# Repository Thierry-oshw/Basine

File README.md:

# Basine
Basine est une carte supportant Ultrogothe et les allumettes. Plusieurs variantes prévues.

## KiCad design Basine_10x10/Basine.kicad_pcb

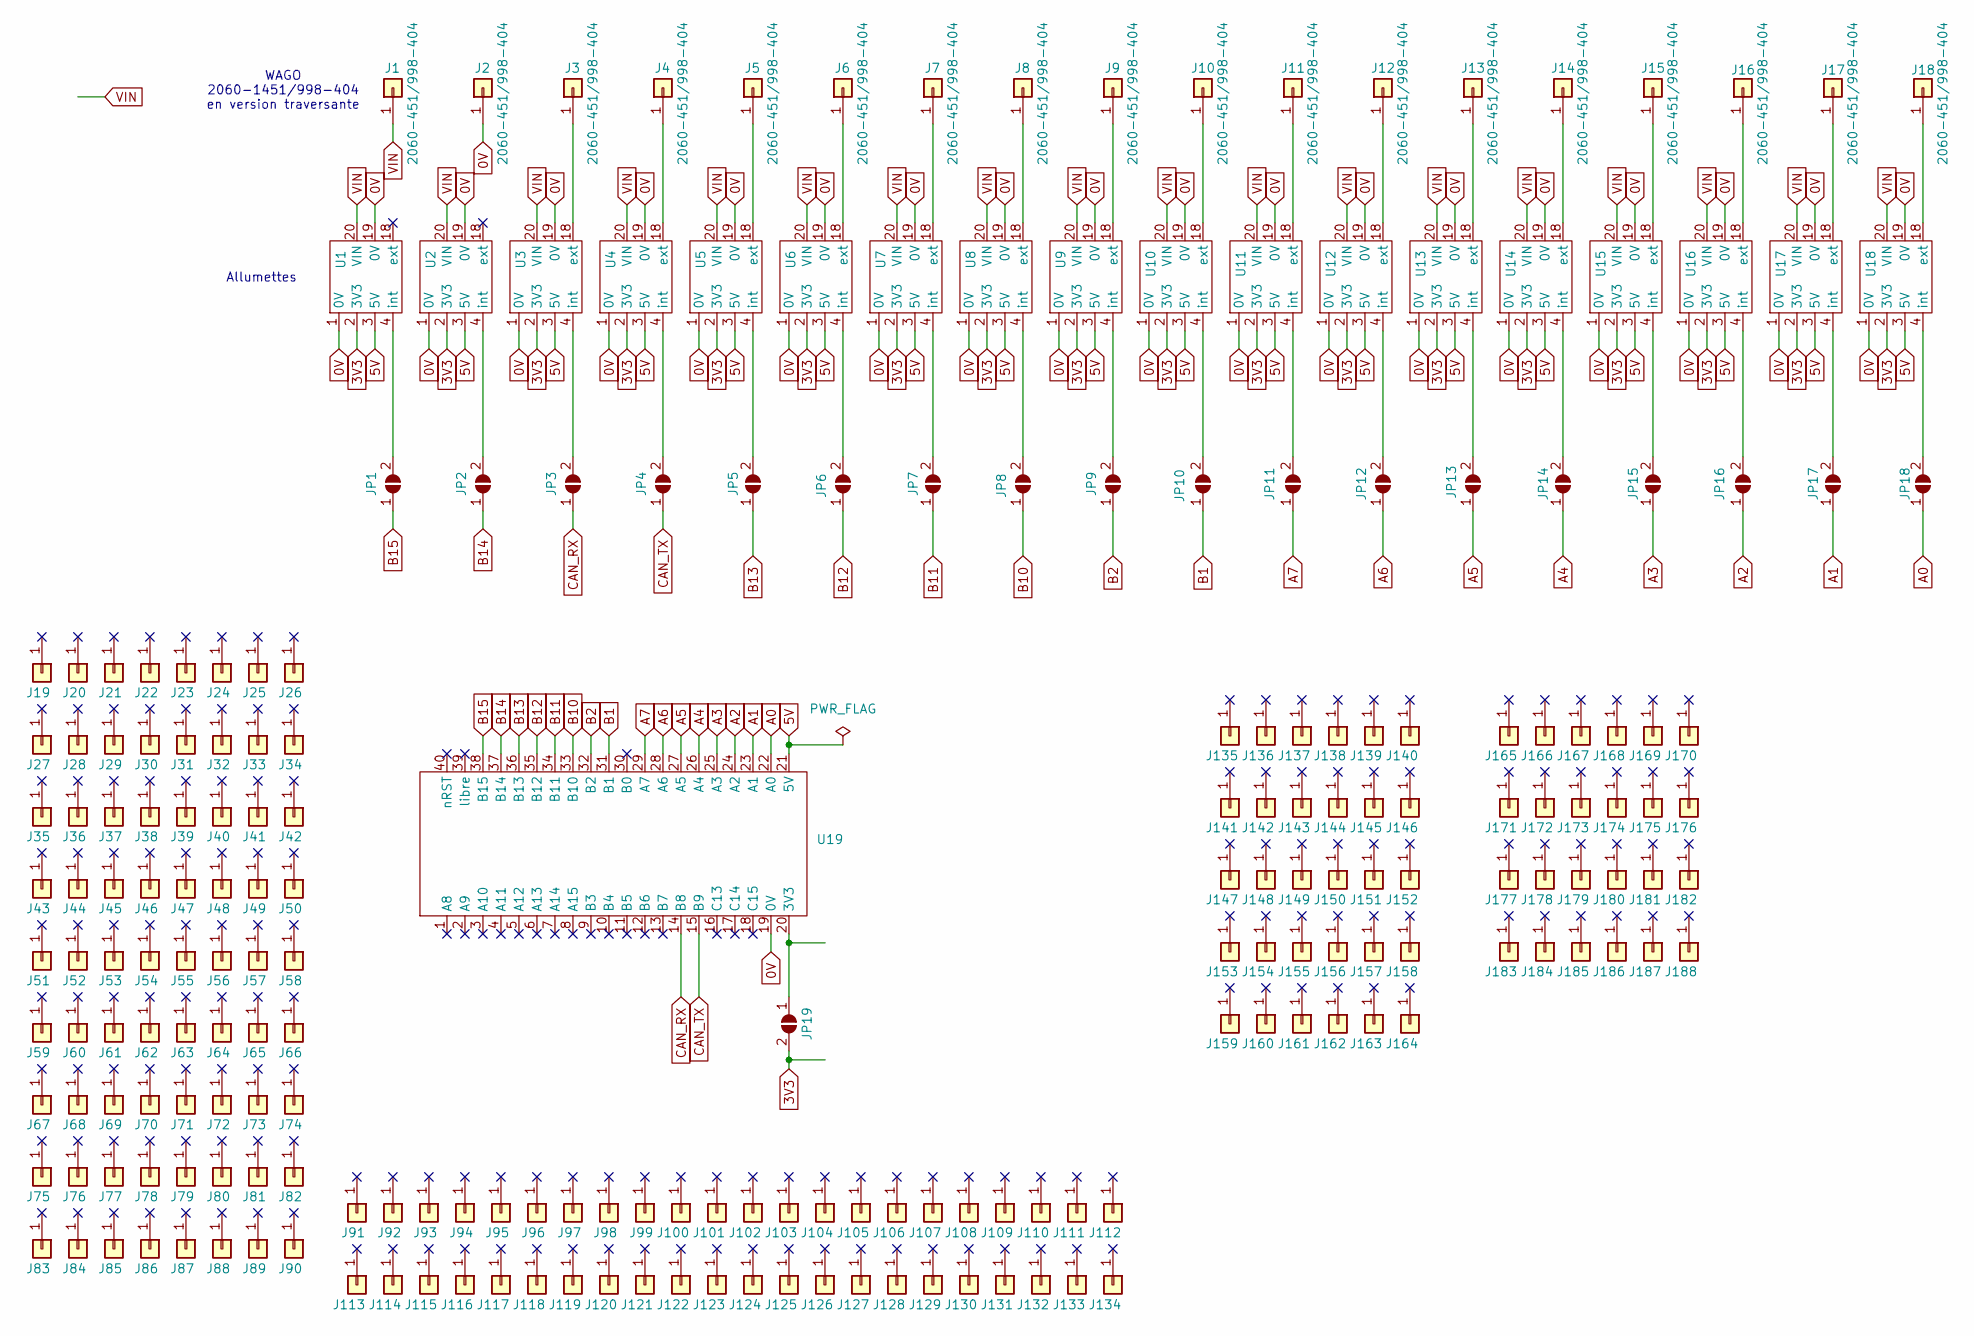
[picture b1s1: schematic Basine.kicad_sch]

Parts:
J1, J2, J3, J4, J5, J6, J7, J8, J9, J10, J11, J12, J13, J14, J15, J16, J17, J18: 2060-451/998-404; Conn_bornier_et_wago
J19, J20, J21, J22, J23, J24, J25, J26, J27, J28, J29, J30, J31, J32, J33, J34, J35, J36, J37, J38, J39, J40, J41, J42, J43, J44, J45, J46, J47, J48, J49, J50, J51, J52, J53, J54, J55, J56, J57, J58, J59, J60, J61, J62, J63, J64, J65, J66, J67, J68, J69, J70, J71, J72, J73, J74, J75, J76, J77, J78, J79, J80, J81, J82, J83, J84, J85, J86, J87, J88, J89, J90, J91, J92, J93, J94, J95, J96, J97, J98, J99, J100, J101, J102, J103, J104, J105, J106, J107, J108, J109, J110, J111, J112, J113, J114, J115, J116, J117, J118, J119, J120, J121, J122, J123, J124, J125, J126, J127, J128, J129, J130, J131, J132, J133, J134, J135, J136, J137, J138, J139, J140, J141, J142, J143, J144, J145, J146, J147, J148, J149, J150, J151, J152, J153, J154, J155, J156, J157, J158, J159, J160, J161, J162, J163, J164, J165, J166, J167, J168, J169, J170, J171, J172, J173, J174, J175, J176, J177, J178, J179, J180, J181, J182, J183, J184, J185, J186, J187, J188: Pastille; Pastille_carree
JP1, JP2, JP3, JP4, JP5, JP6, JP7, JP8, JP9, JP10, JP11, JP12, JP13, JP14, JP15, JP16, JP17, JP18, JP19: SolderJumper_2_Open; SolderJumper-2_P1.3mm_Open_TrianglePad1.0x1.5mm
U1, U2, U3, U4, U5, U6, U7, U8, U9, U10, U11, U12, U13, U14, U15, U16, U17, U18: Allumette
U19: Ultrogothe

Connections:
0V: J2.1, U1.1 (0V), U1.19 (0V), U2.1 (0V), U2.19 (0V), U3.1 (0V), U3.19 (0V), U4.1 (0V), U4.19 (0V), U5.1 (0V), U5.19 (0V), U6.1 (0V), U6.19 (0V), U7.1 (0V), U7.19 (0V), U8.1 (0V), U8.19 (0V), U9.1 (0V), U9.19 (0V), U10.1 (0V), U10.19 (0V), U11.1 (0V), U11.19 (0V), U12.1 (0V), U12.19 (0V), U13.1 (0V), U13.19 (0V), U14.1 (0V), U14.19 (0V), U15.1 (0V), U15.19 (0V), U16.1 (0V), U16.19 (0V), U17.1 (0V), U17.19 (0V), U18.1 (0V), U18.19 (0V), U19.19 (0V)
3V3: JP19.2 (B), U1.2 (3V3), U2.2 (3V3), U3.2 (3V3), U4.2 (3V3), U5.2 (3V3), U6.2 (3V3), U7.2 (3V3), U8.2 (3V3), U9.2 (3V3), U10.2 (3V3), U11.2 (3V3), U12.2 (3V3), U13.2 (3V3), U14.2 (3V3), U15.2 (3V3), U16.2 (3V3), U17.2 (3V3), U18.2 (3V3)
5V: U1.3 (5V), U2.3 (5V), U3.3 (5V), U4.3 (5V), U5.3 (5V), U6.3 (5V), U7.3 (5V), U8.3 (5V), U9.3 (5V), U10.3 (5V), U11.3 (5V), U12.3 (5V), U13.3 (5V), U14.3 (5V), U15.3 (5V), U16.3 (5V), U17.3 (5V), U18.3 (5V), U19.21 (5V)
A0: JP18.1 (A), U19.22 (A0)
A1: JP17.1 (A), U19.23 (A1)
A2: JP16.1 (A), U19.24 (A2)
A3: JP15.1 (A), U19.25 (A3)
A4: JP14.1 (A), U19.26 (A4)
A5: JP13.1 (A), U19.27 (A5)
A6: JP12.1 (A), U19.28 (A6)
A7: JP11.1 (A), U19.29 (A7)
B1: JP10.1 (A), U19.31 (B1)
B2: JP9.1 (A), U19.32 (B2)
B10: JP8.1 (A), U19.33 (B10)
B11: JP7.1 (A), U19.34 (B11)
B12: JP6.1 (A), U19.35 (B12)
B13: JP5.1 (A), U19.36 (B13)
B14: JP2.1 (A), U19.37 (B14)
B15: JP1.1 (A), U19.38 (B15)
CAN_RX: JP3.1 (A), U19.14 (B8)
CAN_TX: JP4.1 (A), U19.15 (B9)
unnamed: J3.1, U3.18 (ext)
unnamed: J4.1, U4.18 (ext)
unnamed: J5.1, U5.18 (ext)
unnamed: J6.1, U6.18 (ext)
unnamed: J7.1, U7.18 (ext)
unnamed: J8.1, U8.18 (ext)
unnamed: J9.1, U9.18 (ext)
unnamed: J10.1, U10.18 (ext)
unnamed: J11.1, U11.18 (ext)
unnamed: J12.1, U12.18 (ext)
unnamed: J13.1, U13.18 (ext)
unnamed: J14.1, U14.18 (ext)
unnamed: J15.1, U15.18 (ext)
unnamed: J16.1, U16.18 (ext)
unnamed: J17.1, U17.18 (ext)
unnamed: J18.1, U18.18 (ext)
unnamed: JP1.2 (B), U1.4 (int)
unnamed: JP2.2 (B), U2.4 (int)
unnamed: JP3.2 (B), U3.4 (int)
unnamed: JP4.2 (B), U4.4 (int)
unnamed: JP5.2 (B), U5.4 (int)
unnamed: JP6.2 (B), U6.4 (int)
unnamed: JP7.2 (B), U7.4 (int)
unnamed: JP8.2 (B), U8.4 (int)
unnamed: JP9.2 (B), U9.4 (int)
unnamed: JP10.2 (B), U10.4 (int)
unnamed: JP11.2 (B), U11.4 (int)
unnamed: JP12.2 (B), U12.4 (int)
unnamed: JP13.2 (B), U13.4 (int)
unnamed: JP14.2 (B), U14.4 (int)
unnamed: JP15.2 (B), U15.4 (int)
unnamed: JP16.2 (B), U16.4 (int)
unnamed: JP17.2 (B), U17.4 (int)
unnamed: JP18.2 (B), U18.4 (int)
unnamed: JP19.1 (A), U19.20 (3V3)
VIN: J1.1, U1.20 (VIN), U2.20 (VIN), U3.20 (VIN), U4.20 (VIN), U5.20 (VIN), U6.20 (VIN), U7.20 (VIN), U8.20 (VIN), U9.20 (VIN), U10.20 (VIN), U11.20 (VIN), U12.20 (VIN), U13.20 (VIN), U14.20 (VIN), U15.20 (VIN), U16.20 (VIN), U17.20 (VIN), U18.20 (VIN)

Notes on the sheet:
WAGO 2060-1451/998-404 en version traversante
Allumettes

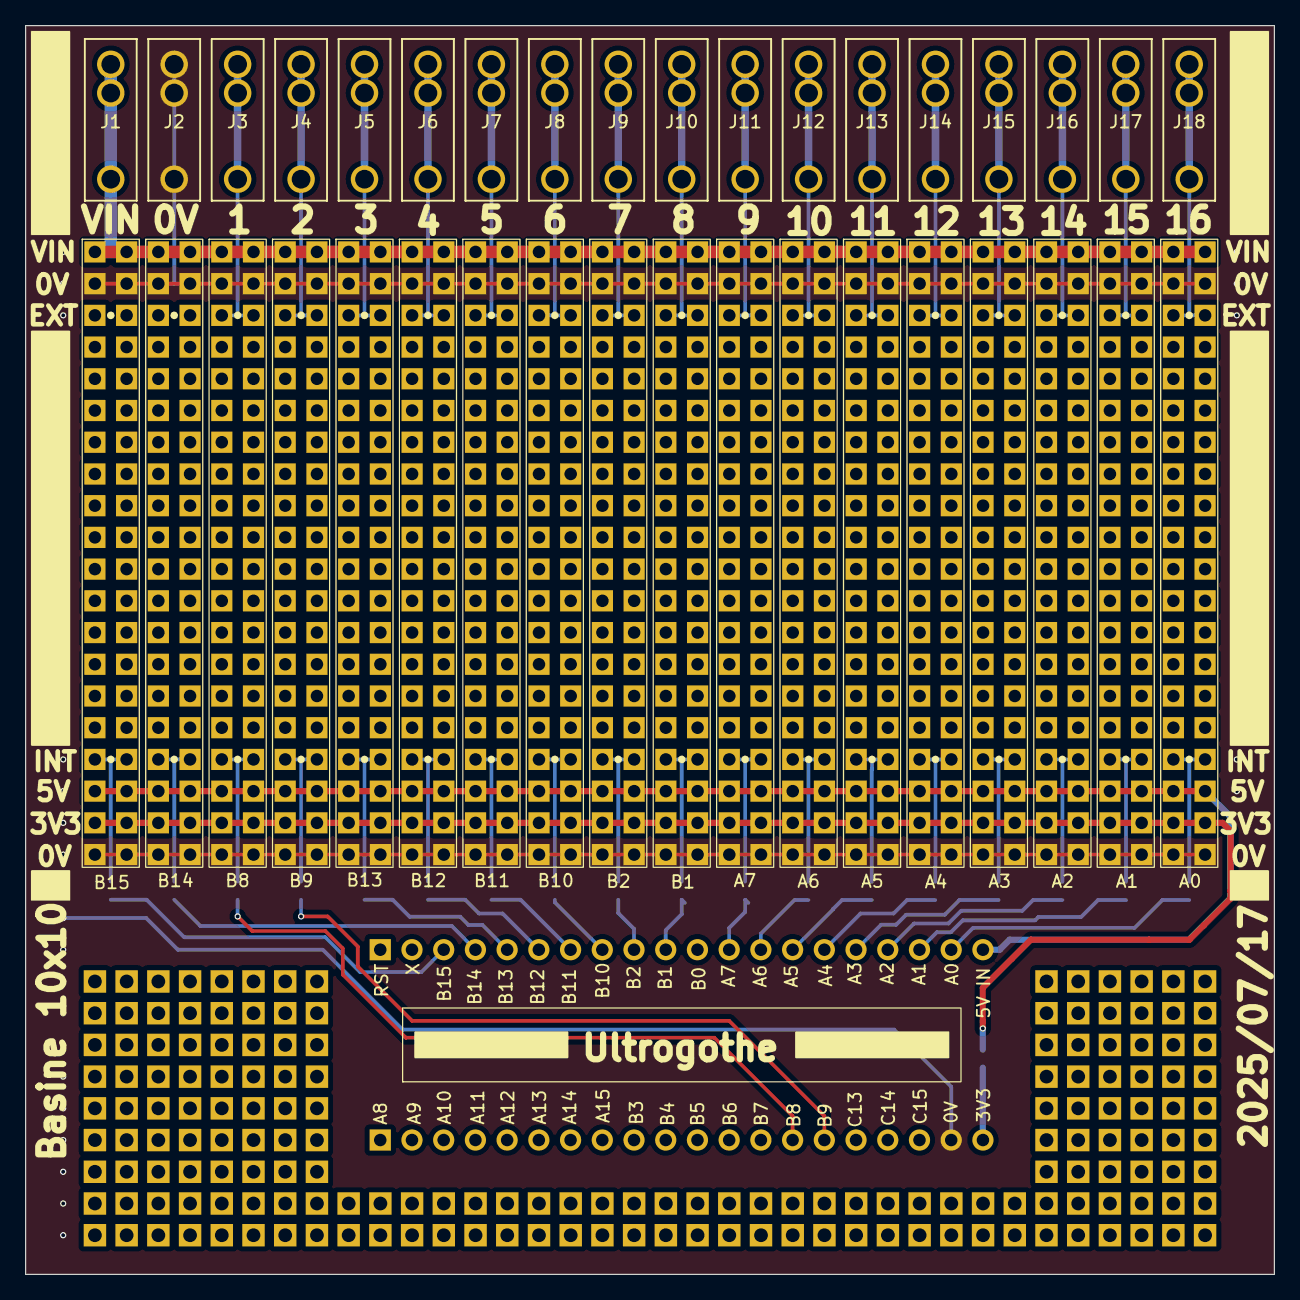
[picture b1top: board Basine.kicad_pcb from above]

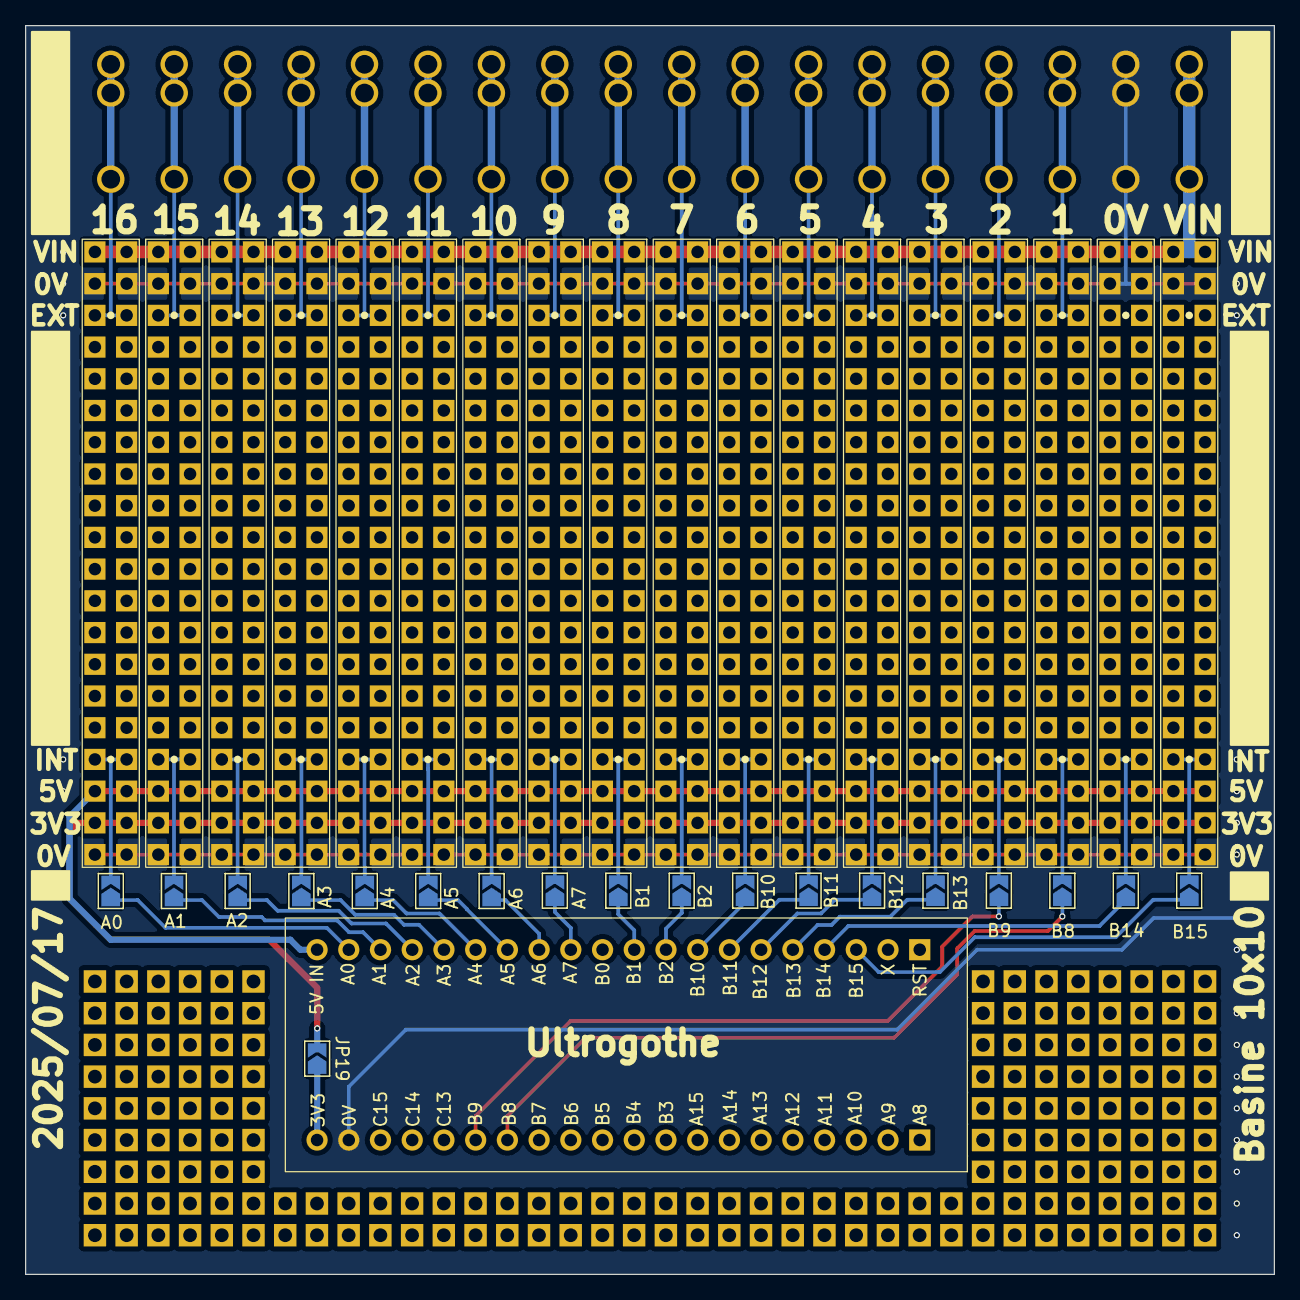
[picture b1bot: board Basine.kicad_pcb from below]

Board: 2 copper layers, 100.0 x 100.0 mm, 226 parts (19 on the bottom side), 57 nets.

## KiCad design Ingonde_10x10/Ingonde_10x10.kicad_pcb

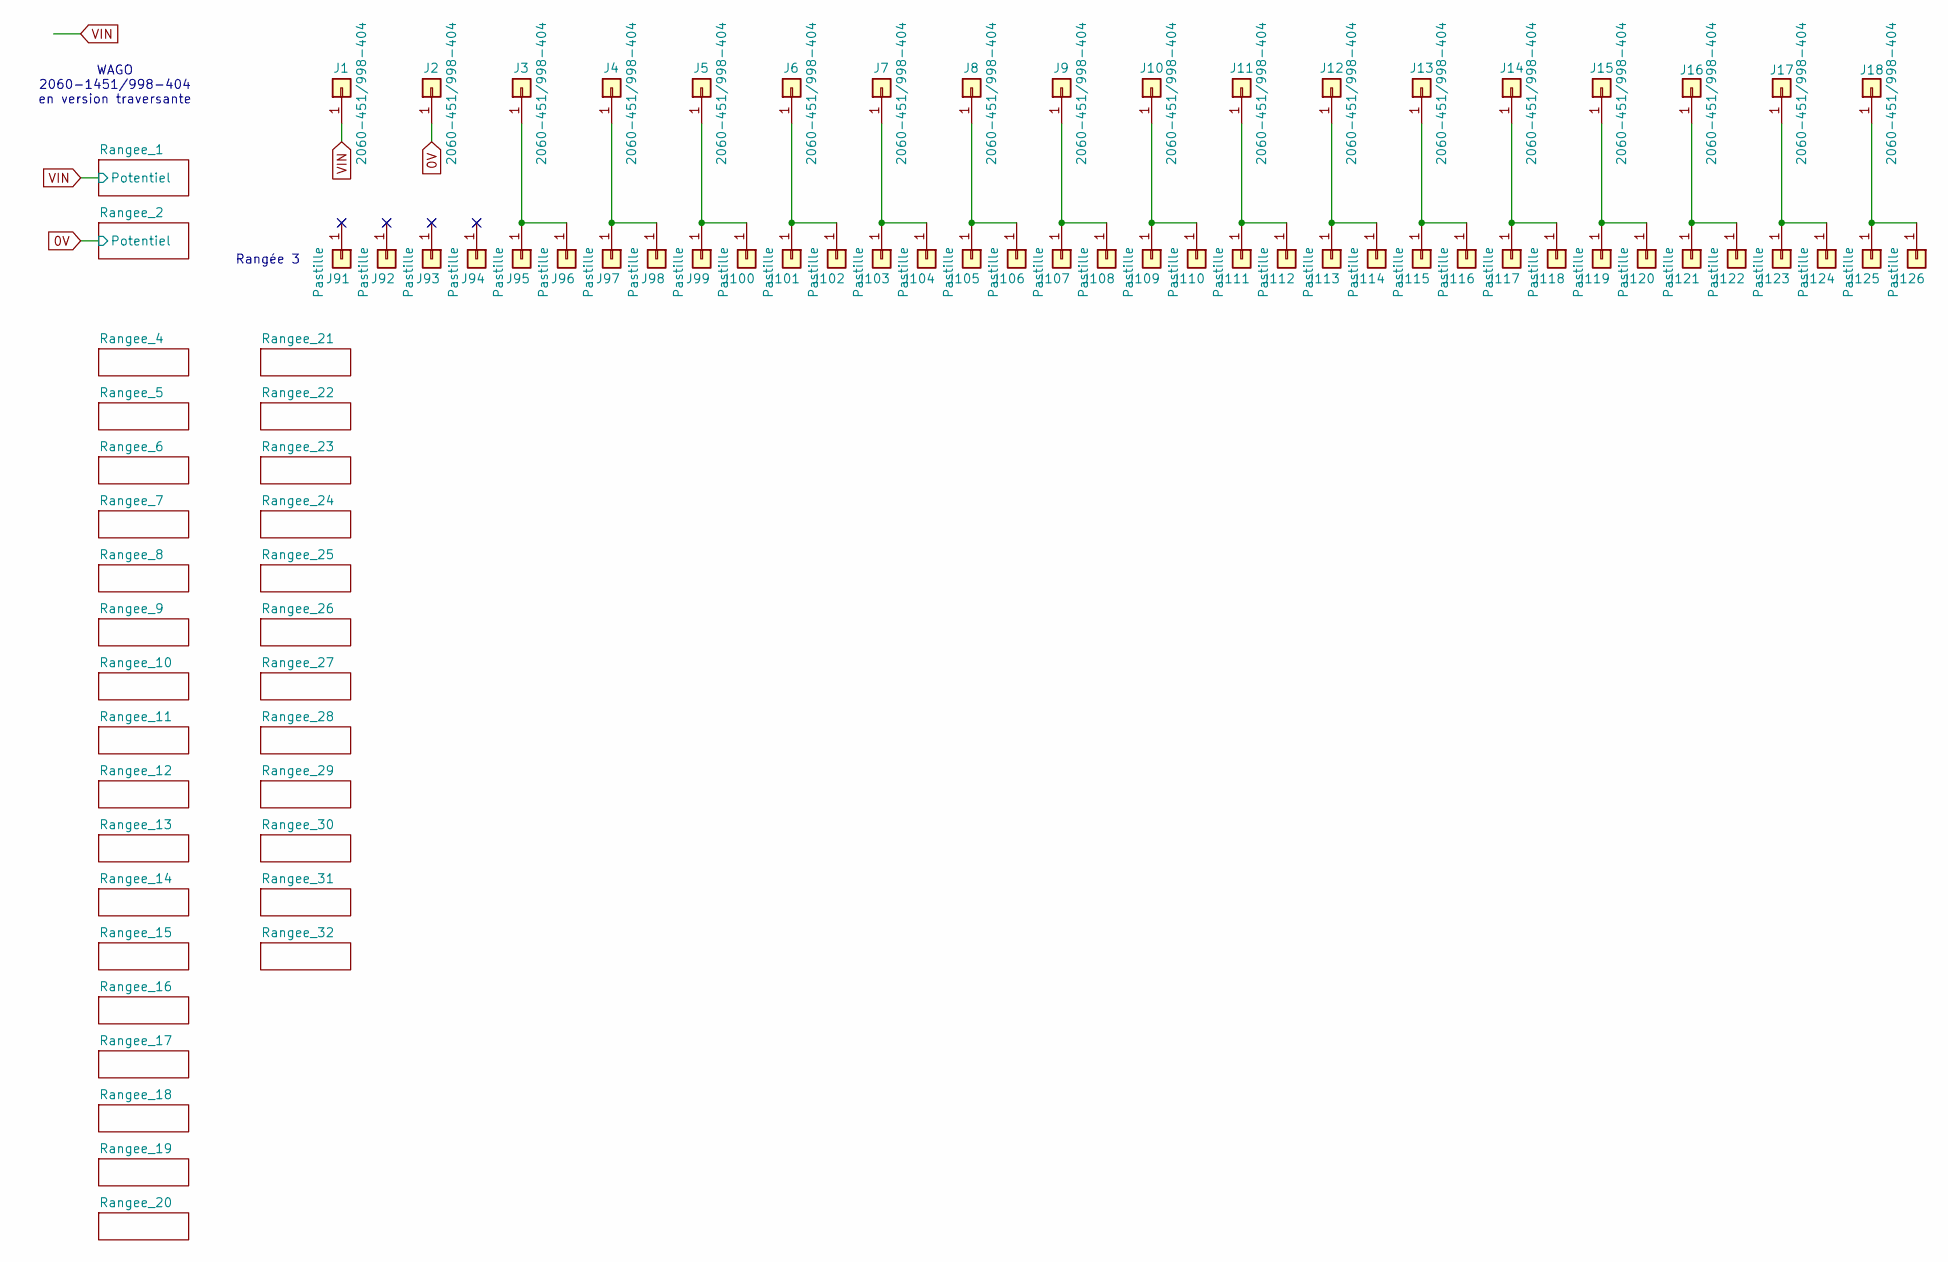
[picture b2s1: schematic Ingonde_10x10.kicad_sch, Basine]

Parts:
J1, J2, J3, J4, J5, J6, J7, J8, J9, J10, J11, J12, J13, J14, J15, J16, J17, J18: 2060-451/998-404; Conn_bornier_et_wago
J91, J92, J93, J94, J95, J96, J97, J98, J99, J100, J101, J102, J103, J104, J105, J106, J107, J108, J109, J110, J111, J112, J113, J114, J115, J116, J117, J118, J119, J120, J121, J122, J123, J124, J125, J126: Pastille; Pastille_carree

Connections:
0V: J2.1; also elsewhere on the board
unnamed: J3.1, J95.1, J96.1
unnamed: J4.1, J97.1, J98.1
unnamed: J10.1, J109.1, J110.1
unnamed: J11.1, J111.1, J112.1
unnamed: J5.1, J99.1, J100.1
unnamed: J6.1, J101.1, J102.1
unnamed: J7.1, J103.1, J104.1
unnamed: J8.1, J105.1, J106.1
unnamed: J9.1, J107.1, J108.1
unnamed: J12.1, J113.1, J114.1
unnamed: J13.1, J115.1, J116.1
unnamed: J14.1, J117.1, J118.1
unnamed: J15.1, J119.1, J120.1
unnamed: J16.1, J121.1, J122.1
unnamed: J17.1, J123.1, J124.1
unnamed: J18.1, J125.1, J126.1
VIN: J1.1; also elsewhere on the board

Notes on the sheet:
WAGO 2060-1451/998-404 en version traversante
Rangée 3

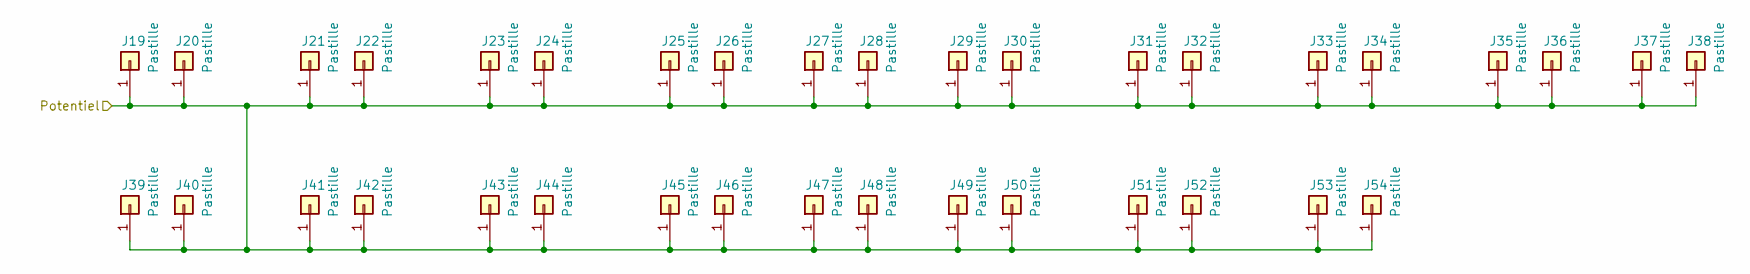
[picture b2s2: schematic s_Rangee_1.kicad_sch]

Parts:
J19, J20, J21, J22, J23, J24, J25, J26, J27, J28, J29, J30, J31, J32, J33, J34, J35, J36, J37, J38, J39, J40, J41, J42, J43, J44, J45, J46, J47, J48, J49, J50, J51, J52, J53, J54: Pastille; Pastille_carree

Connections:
VIN: J19.1, J20.1, J21.1, J22.1, J23.1, J24.1, J25.1, J26.1, J27.1, J28.1, J29.1, J30.1, J31.1, J32.1, J33.1, J34.1, J35.1, J36.1, J37.1, J38.1, J39.1, J40.1, J41.1, J42.1, J43.1, J44.1, J45.1, J46.1, J47.1, J48.1, J49.1, J50.1, J51.1, J52.1, J53.1, J54.1; also elsewhere on the board

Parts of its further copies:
J55, J56, J57, J58, J59, J60, J61, J62, J63, J64, J65, J66, J67, J68, J69, J70, J71, J72, J73, J74, J75, J76, J77, J78, J79, J80, J81, J82, J83, J84, J85, J86, J87, J88, J89, J90: Pastille; Pastille_carree

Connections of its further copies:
0V: J55.1, J56.1, J57.1, J58.1, J59.1, J60.1, J61.1, J62.1, J63.1, J64.1, J65.1, J66.1, J67.1, J68.1, J69.1, J70.1, J71.1, J72.1, J73.1, J74.1, J75.1, J76.1, J77.1, J78.1, J79.1, J80.1, J81.1, J82.1, J83.1, J84.1, J85.1, J86.1, J87.1, J88.1, J89.1, J90.1; also elsewhere on the board

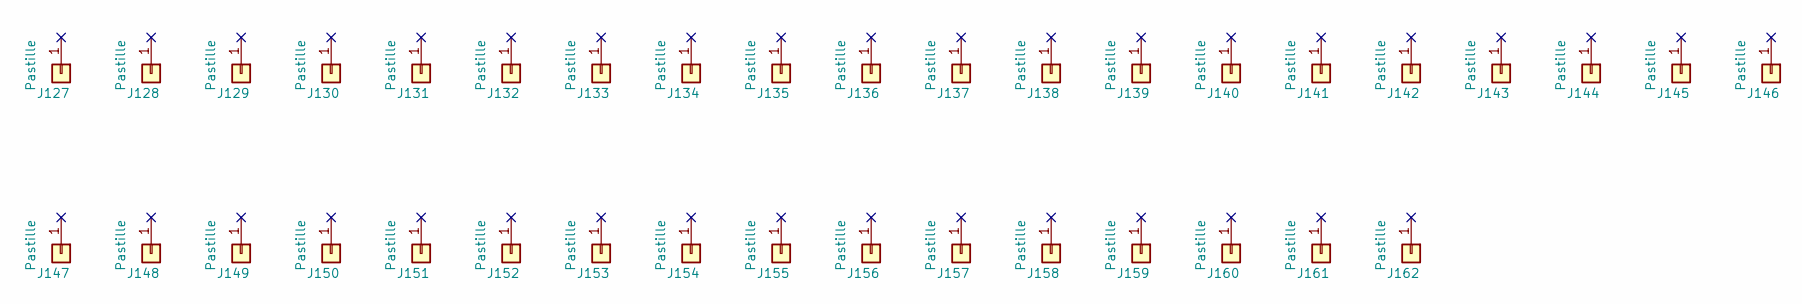
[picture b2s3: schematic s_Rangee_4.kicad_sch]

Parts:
J127, J128, J129, J130, J131, J132, J133, J134, J135, J136, J137, J138, J139, J140, J141, J142, J143, J144, J145, J146, J147, J148, J149, J150, J151, J152, J153, J154, J155, J156, J157, J158, J159, J160, J161, J162: Pastille; Pastille_carree

Parts of its further copies:
J163, J164, J165, J166, J167, J168, J169, J170, J171, J172, J173, J174, J175, J176, J177, J178, J179, J180, J181, J182, J183, J184, J185, J186, J187, J188, J189, J190, J191, J192, J193, J194, J195, J196, J197, J198, J199, J200, J201, J202, J203, J204, J205, J206, J207, J208, J209, J210, J211, J212, J213, J214, J215, J216, J217, J218, J219, J220, J221, J222, J223, J224, J225, J226, J227, J228, J229, J230, J231, J232, J233, J234, J235, J236, J237, J238, J239, J240, J241, J242, J243, J244, J245, J246, J247, J248, J249, J250, J251, J252, J253, J254, J255, J256, J257, J258, J259, J260, J261, J262, J263, J264, J265, J266, J267, J268, J269, J270, J271, J272, J273, J274, J275, J276, J277, J278, J279, J280, J281, J282, J283, J284, J285, J286, J287, J288, J289, J290, J291, J292, J293, J294, J295, J296, J297, J298, J299, J300, J301, J302, J303, J304, J305, J306, J307, J308, J309, J310, J311, J312, J313, J314, J315, J316, J317, J318, J319, J320, J321, J322, J323, J324, J325, J326, J327, J328, J329, J330, J331, J332, J333, J334, J335, J336, J337, J338, J339, J340, J341, J342, J343, J344, J345, J346, J347, J348, J349, J350, J351, J352, J353, J354, J355, J356, J357, J358, J359, J360, J361, J362, J363, J364, J365, J366, J367, J368, J369, J370, J371, J372, J373, J374, J375, J376, J377, J378, J379, J380, J381, J382, J383, J384, J385, J386, J387, J388, J389, J390, J391, J392, J393, J394, J395, J396, J397, J398, J399, J400, J401, J402, J403, J404, J405, J406, J407, J408, J409, J410, J411, J412, J413, J414, J415, J416, J417, J418, J419, J420, J421, J422, J423, J424, J425, J426, J427, J428, J429, J430, J431, J432, J433, J434, J435, J436, J437, J438, J439, J440, J441, J442, J443, J444, J445, J446, J447, J448, J449, J450, J451, J452, J453, J454, J455, J456, J457, J458, J459, J460, J461, J462, J463, J464, J465, J466, J467, J468, J469, J470, J471, J472, J473, J474, J475, J476, J477, J478, J479, J480, J481, J482, J483, J484, J485, J486, J487, J488, J489, J490, J491, J492, J493, J494, J495, J496, J497, J498, J499, J500, J501, J502, J503, J504, J505, J506, J507, J508, J509, J510, J511, J512, J513, J514, J515, J516, J517, J518, J519, J520, J521, J522, J523, J524, J525, J526, J527, J528, J529, J530, J531, J532, J533, J534, J535, J536, J537, J538, J539, J540, J541, J542, J543, J544, J545, J546, J547, J548, J549, J550, J551, J552, J553, J554, J555, J556, J557, J558, J559, J560, J561, J562, J563, J564, J565, J566, J567, J568, J569, J570, J571, J572, J573, J574, J575, J576, J577, J578, J579, J580, J581, J582, J583, J584, J585, J586, J587, J588, J589, J590, J591, J592, J593, J594, J595, J596, J597, J598, J599, J600, J601, J602, J603, J604, J605, J606, J607, J608, J609, J610, J611, J612, J613, J614, J615, J616, J617, J618, J619, J620, J621, J622, J623, J624, J625, J626, J627, J628, J629, J630, J631, J632, J633, J634, J635, J636, J637, J638, J639, J640, J641, J642, J643, J644, J645, J646, J647, J648, J649, J650, J651, J652, J653, J654, J655, J656, J657, J658, J659, J660, J661, J662, J663, J664, J665, J666, J667, J668, J669, J670, J671, J672, J673, J674, J675, J676, J677, J678, J679, J680, J681, J682, J683, J684, J685, J686, J687, J688, J689, J690, J691, J692, J693, J694, J695, J696, J697, J698, J699, J700, J701, J702, J703, J704, J705, J706, J707, J708, J709, J710, J711, J712, J713, J714, J715, J716, J717, J718, J719, J720, J721, J722, J723, J724, J725, J726, J727, J728, J729, J730, J731, J732, J733, J734, J735, J736, J737, J738, J739, J740, J741, J742, J743, J744, J745, J746, J747, J748, J749, J750, J751, J752, J753, J754, J755, J756, J757, J758, J759, J760, J761, J762, J763, J764, J765, J766, J767, J768, J769, J770, J771, J772, J773, J774, J775, J776, J777, J778, J779, J780, J781, J782, J783, J784, J785, J786, J787, J788, J789, J790, J791, J792, J793, J794, J795, J796, J797, J798, J799, J800, J801, J802, J803, J804, J805, J806, J807, J808, J809, J810, J811, J812, J813, J814, J815, J816, J817, J818, J819, J820, J821, J822, J823, J824, J825, J826, J827, J828, J829, J830, J831, J832, J833, J834, J835, J836, J837, J838, J839, J840, J841, J842, J843, J844, J845, J846, J847, J848, J849, J850, J851, J852, J853, J854, J855, J856, J857, J858, J859, J860, J861, J862, J863, J864, J865, J866, J867, J868, J869, J870, J871, J872, J873, J874, J875, J876, J877, J878, J879, J880, J881, J882, J883, J884, J885, J886, J887, J888, J889, J890, J891, J892, J893, J894, J895, J896, J897, J898, J899, J900, J901, J902, J903, J904, J905, J906, J907, J908, J909, J910, J911, J912, J913, J914, J915, J916, J917, J918, J919, J920, J921, J922, J923, J924, J925, J926, J927, J928, J929, J930, J931, J932, J933, J934, J935, J936, J937, J938, J939, J940, J941, J942, J943, J944, J945, J946, J947, J948, J949, J950, J951, J952, J953, J954, J955, J956, J957, J958, J959, J960, J961, J962, J963, J964, J965, J966, J967, J968, J969, J970, J971, J972, J973, J974, J975, J976, J977, J978, J979, J980, J981, J982, J983, J984, J985, J986, J987, J988, J989, J990, J991, J992, J993, J994, J995, J996, J997, J998, J999, J1000, J1001, J1002, J1003, J1004, J1005, J1006, J1007, J1008, J1009, J1010, J1011, J1012, J1013, J1014, J1015, J1016, J1017, J1018, J1019, J1020, J1021, J1022, J1023, J1024, J1025, J1026, J1027, J1028, J1029, J1030, J1031, J1032, J1033, J1034, J1035, J1036, J1037, J1038, J1039, J1040, J1041, J1042, J1043, J1044, J1045, J1046, J1047, J1048, J1049, J1050, J1051, J1052, J1053, J1054, J1055, J1056, J1057, J1058, J1059, J1060, J1061, J1062, J1063, J1064, J1065, J1066, J1067, J1068, J1069, J1070, J1071, J1072, J1073, J1074, J1075, J1076, J1077, J1078, J1079, J1080, J1081, J1082, J1083, J1084, J1085, J1086, J1087, J1088, J1089, J1090, J1091, J1092, J1093, J1094, J1095, J1096, J1097, J1098, J1099, J1100, J1101, J1102, J1103, J1104, J1105, J1106, J1107, J1108, J1109, J1110, J1111, J1112, J1113, J1114, J1115, J1116, J1117, J1118, J1119, J1120, J1121, J1122, J1123, J1124, J1125, J1126, J1127, J1128, J1129, J1130, J1131, J1132, J1133, J1134, J1135, J1136, J1137, J1138, J1139, J1140, J1141, J1142, J1143, J1144, J1145, J1146, J1147, J1148, J1149, J1150, J1151, J1152, J1153, J1154, J1155, J1156, J1157, J1158, J1159, J1160, J1161, J1162, J1163, J1164, J1165, J1166, J1167, J1168, J1169, J1170: Pastille; Pastille_carree

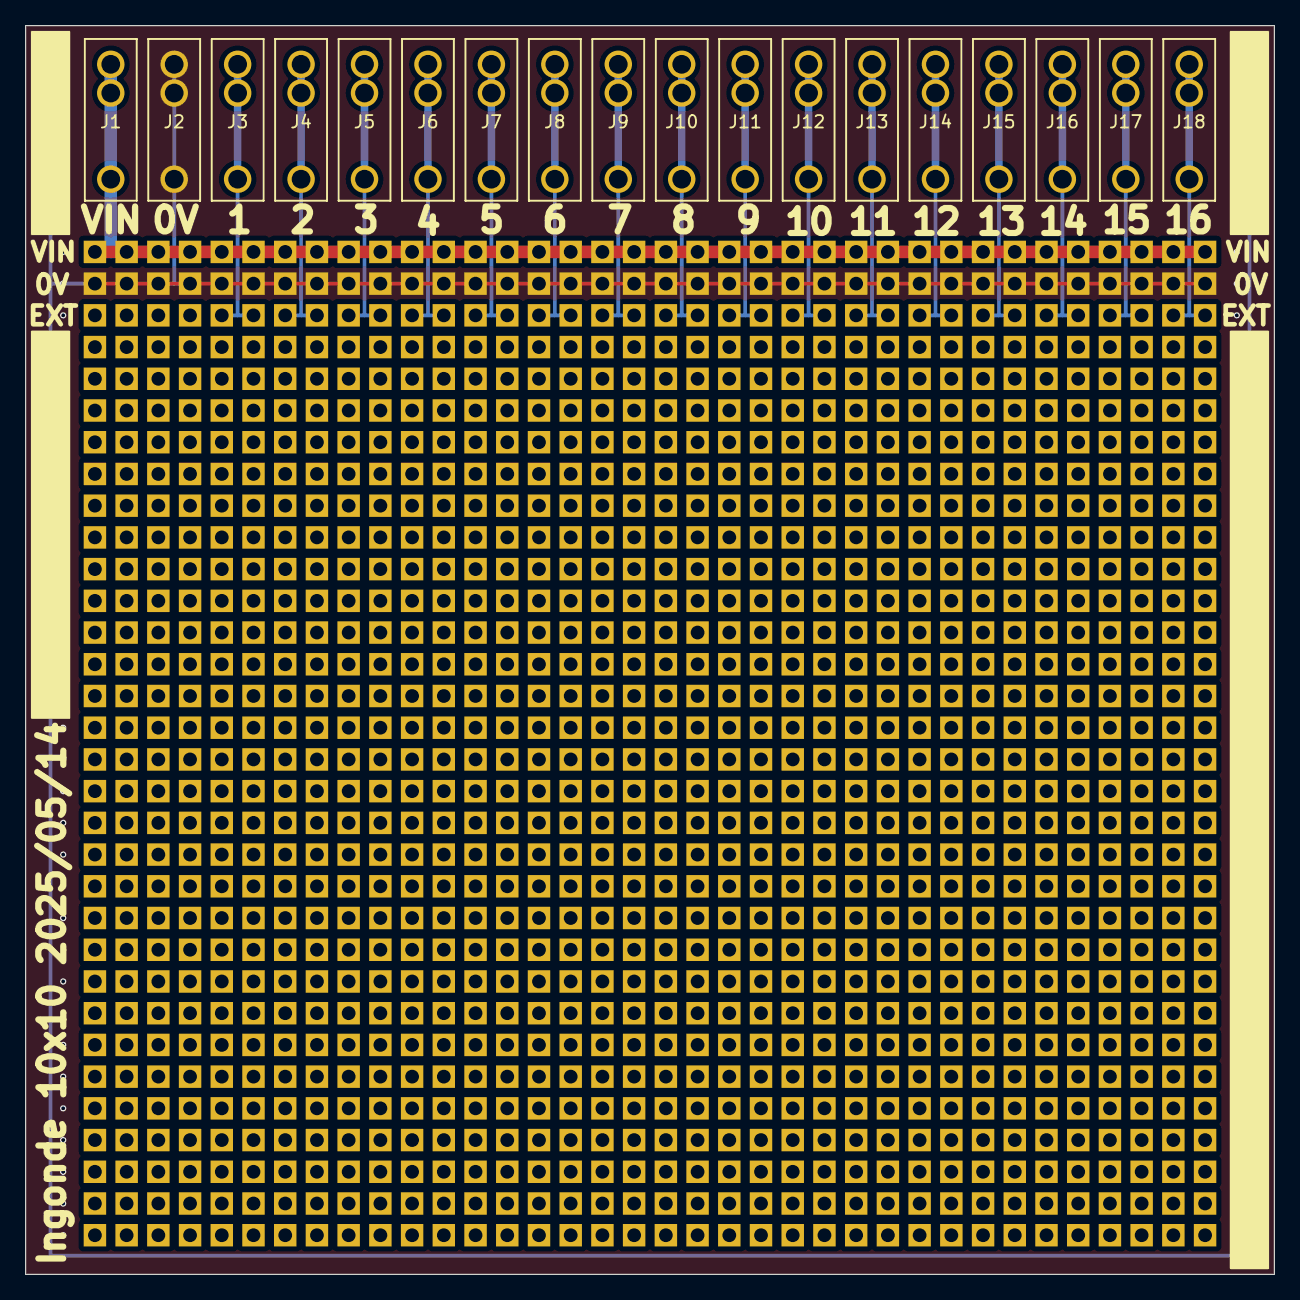
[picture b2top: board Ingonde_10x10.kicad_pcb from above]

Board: 2 copper layers, 100.0 x 100.0 mm, 1170 parts (0 on the bottom side), 18 nets.

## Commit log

2024-12-13 Basine_10x10
    premier jet
2024-12-15 Basine_10x10 :
    ajout ultrogothe
2024-12-15 Basine_10x10
    ajout symbole ultrogothe
    ajout power flag sur 5V
2024-12-30 10x10
    ajout empreinte ultrogothe
    placement ultrogothe et un peu alim 5V
2024-12-31 10x10
    placement et routage du CAN
    divers
2025-01-01 Update Basine.kicad_pcb
    alignement et routage des jumpers
2025-01-01 Update Basine.kicad_pcb
    divers routage
2025-01-01 10x10
    alim 5V ok
    placement et routage ok
    reste vias à placer
2025-01-03 10x10
    passe vias et plans
    indications sur silk
2025-01-03 10x10
    tentative de fabrication
    pénurie spring clamp à gérer
2025-01-03 10x10
    ajout ref traversante de wago
2025-01-03 10x10
    chgt connecteur wago
    fabrication
2025-04-21 passage au pas de 2,54mm pour toutes les allumettes
2025-04-21 ignore lck file
2025-05-01 Basine 10x10 : enlever DCDC et CAN
2025-05-01 Basine_10x10 : placement et routage
2025-05-01 Ingonde 10x10 : création
2025-05-01 Ingonde 10x10 : passage à kicad 9.0.1
2025-05-02 Ingonde : fin matrice, pastille carrée, vias a 2,54mm
2025-05-07 Basine_10x10 : moins de vias
2025-05-07 Ingonde_10x10 : moins de vias
2025-05-14 Ingonde_10x10: doublage des connecteurs
2025-05-14 Ingonde_10x10: fabrication
2025-05-30 plaque 10x20 : premier jet
2025-05-30 plaque 12_5x20 : premier jet
2025-07-07 Basine 10x10: modification ultrogothe, allumettes, 3v3 en option
2025-07-16 Basine_10x10 : recentrage ultro et ajout zone proto
2025-07-17 maj ultrogothe et fabrication
2026-02-02 Basine : maj kicad
2026-02-02 Ingonde : maj kicad
